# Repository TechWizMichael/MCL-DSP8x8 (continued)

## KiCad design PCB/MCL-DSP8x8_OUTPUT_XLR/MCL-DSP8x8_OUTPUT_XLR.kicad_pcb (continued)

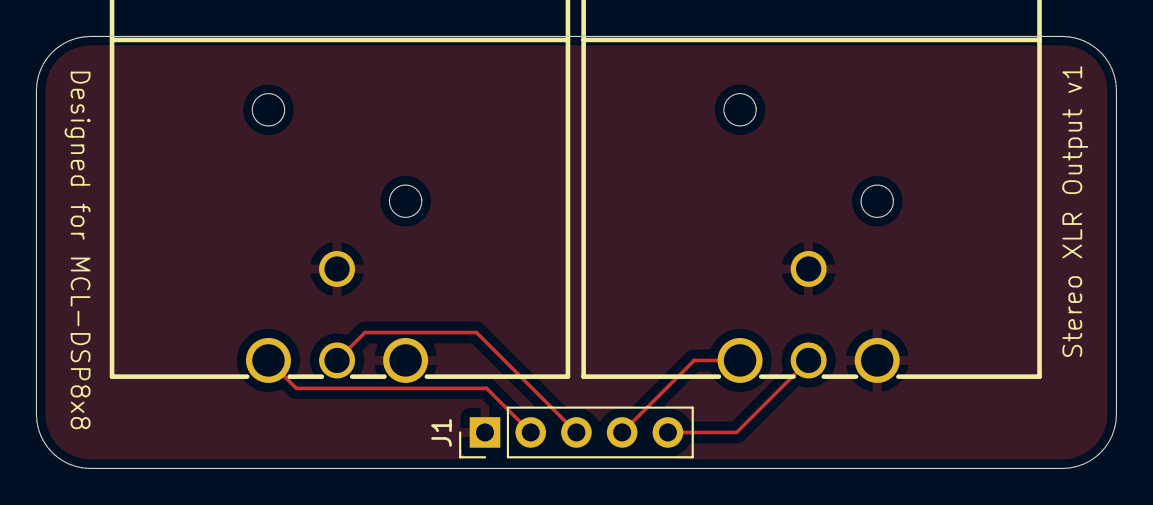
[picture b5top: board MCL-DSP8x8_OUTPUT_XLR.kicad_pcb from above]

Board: 2 copper layers, 60.0 x 24.0 mm, 3 parts (0 on the bottom side), 5 nets.

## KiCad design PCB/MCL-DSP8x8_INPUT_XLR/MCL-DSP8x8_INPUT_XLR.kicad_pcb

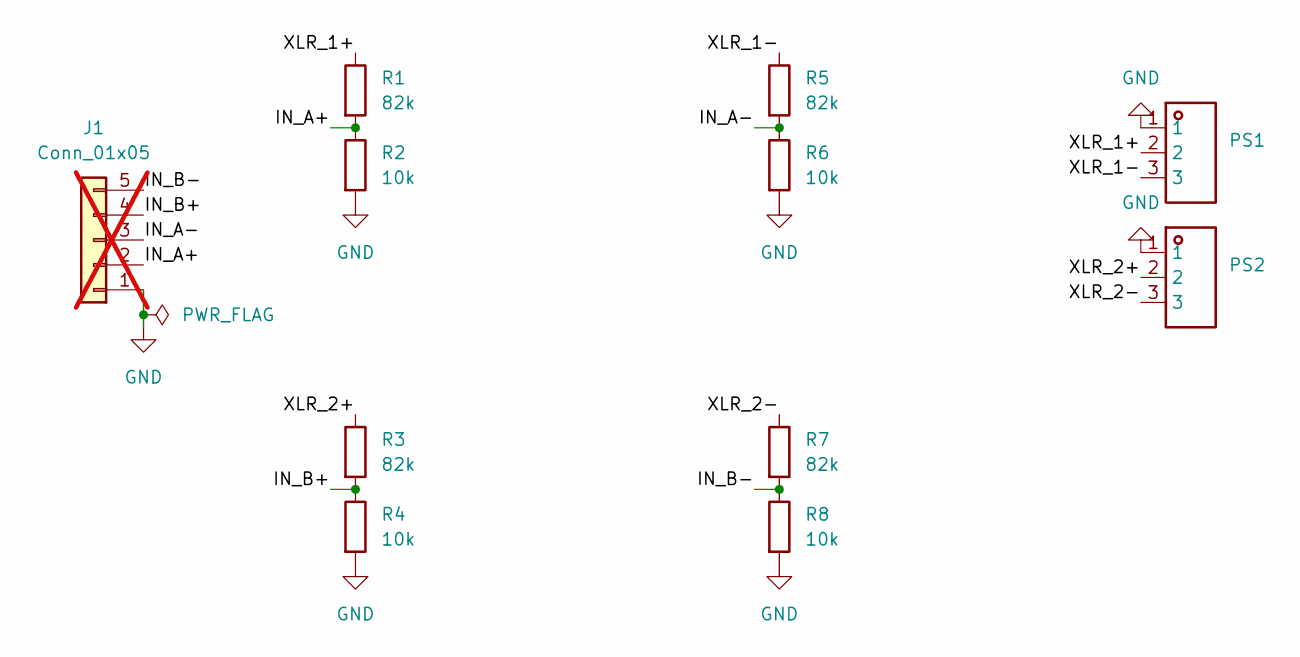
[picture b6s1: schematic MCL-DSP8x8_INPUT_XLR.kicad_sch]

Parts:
J1: Conn_01x05; PinHeader_1x05_P2.54mm_Vertical; not fitted
PS1, PS2: NC3FAAH1; Manufacturer Part NC3FAAH1; LCSC Part Name NC3FAAH1
R1, R3, R5, R7: 82k; R_0805_2012Metric_Pad1.20x1.40mm_HandSolder; LCSC Part # C22356755
R2, R4, R6, R8: 10k; R_0805_2012Metric_Pad1.20x1.40mm_HandSolder; LCSC Part # C3152175

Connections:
/IN_A+: J1.2, R1.2, R2.1
/IN_A-: J1.3, R5.2, R6.1
/IN_B+: J1.4, R3.2, R4.1
/IN_B-: J1.5, R7.2, R8.1
/XLR_1+: PS1.2, R1.1
/XLR_1-: PS1.3, R5.1
/XLR_2+: PS2.2, R3.1
/XLR_2-: PS2.3, R7.1
GND: J1.1, PS1.1, PS2.1, R2.2, R4.2, R6.2, R8.2

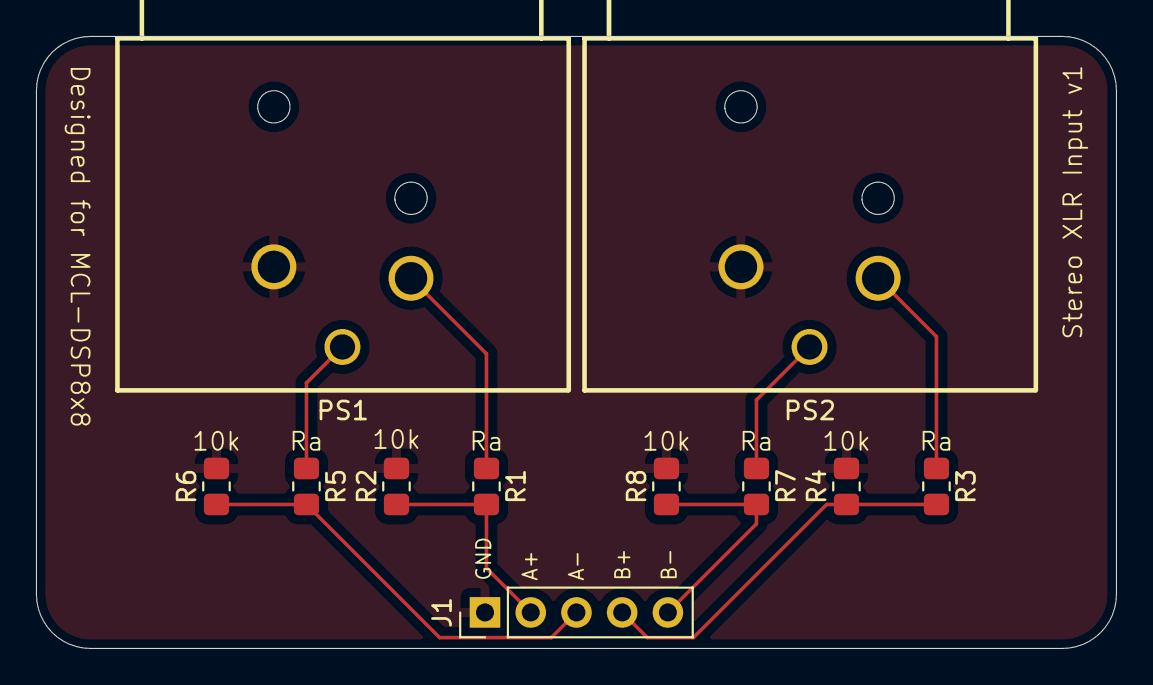
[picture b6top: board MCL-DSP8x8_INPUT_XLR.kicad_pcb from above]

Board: 2 copper layers, 60.0 x 34.0 mm, 11 parts (0 on the bottom side), 9 nets.

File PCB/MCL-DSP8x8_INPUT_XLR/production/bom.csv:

Designator,Footprint,Quantity,Value,LCSC Part #
J1,PinHeader_1x05_P2.54mm_Vertical,1,Conn_01x05,
"PS1, PS2",NC3FAAH1,2,~,
"R1, R3, R5, R7",R_Axial_DIN0207_L6.3mm_D2.5mm_P10.16mm_Horizontal,4,82k,
"R2, R4, R6, R8",R_Axial_DIN0207_L6.3mm_D2.5mm_P10.16mm_Horizontal,4,10k,

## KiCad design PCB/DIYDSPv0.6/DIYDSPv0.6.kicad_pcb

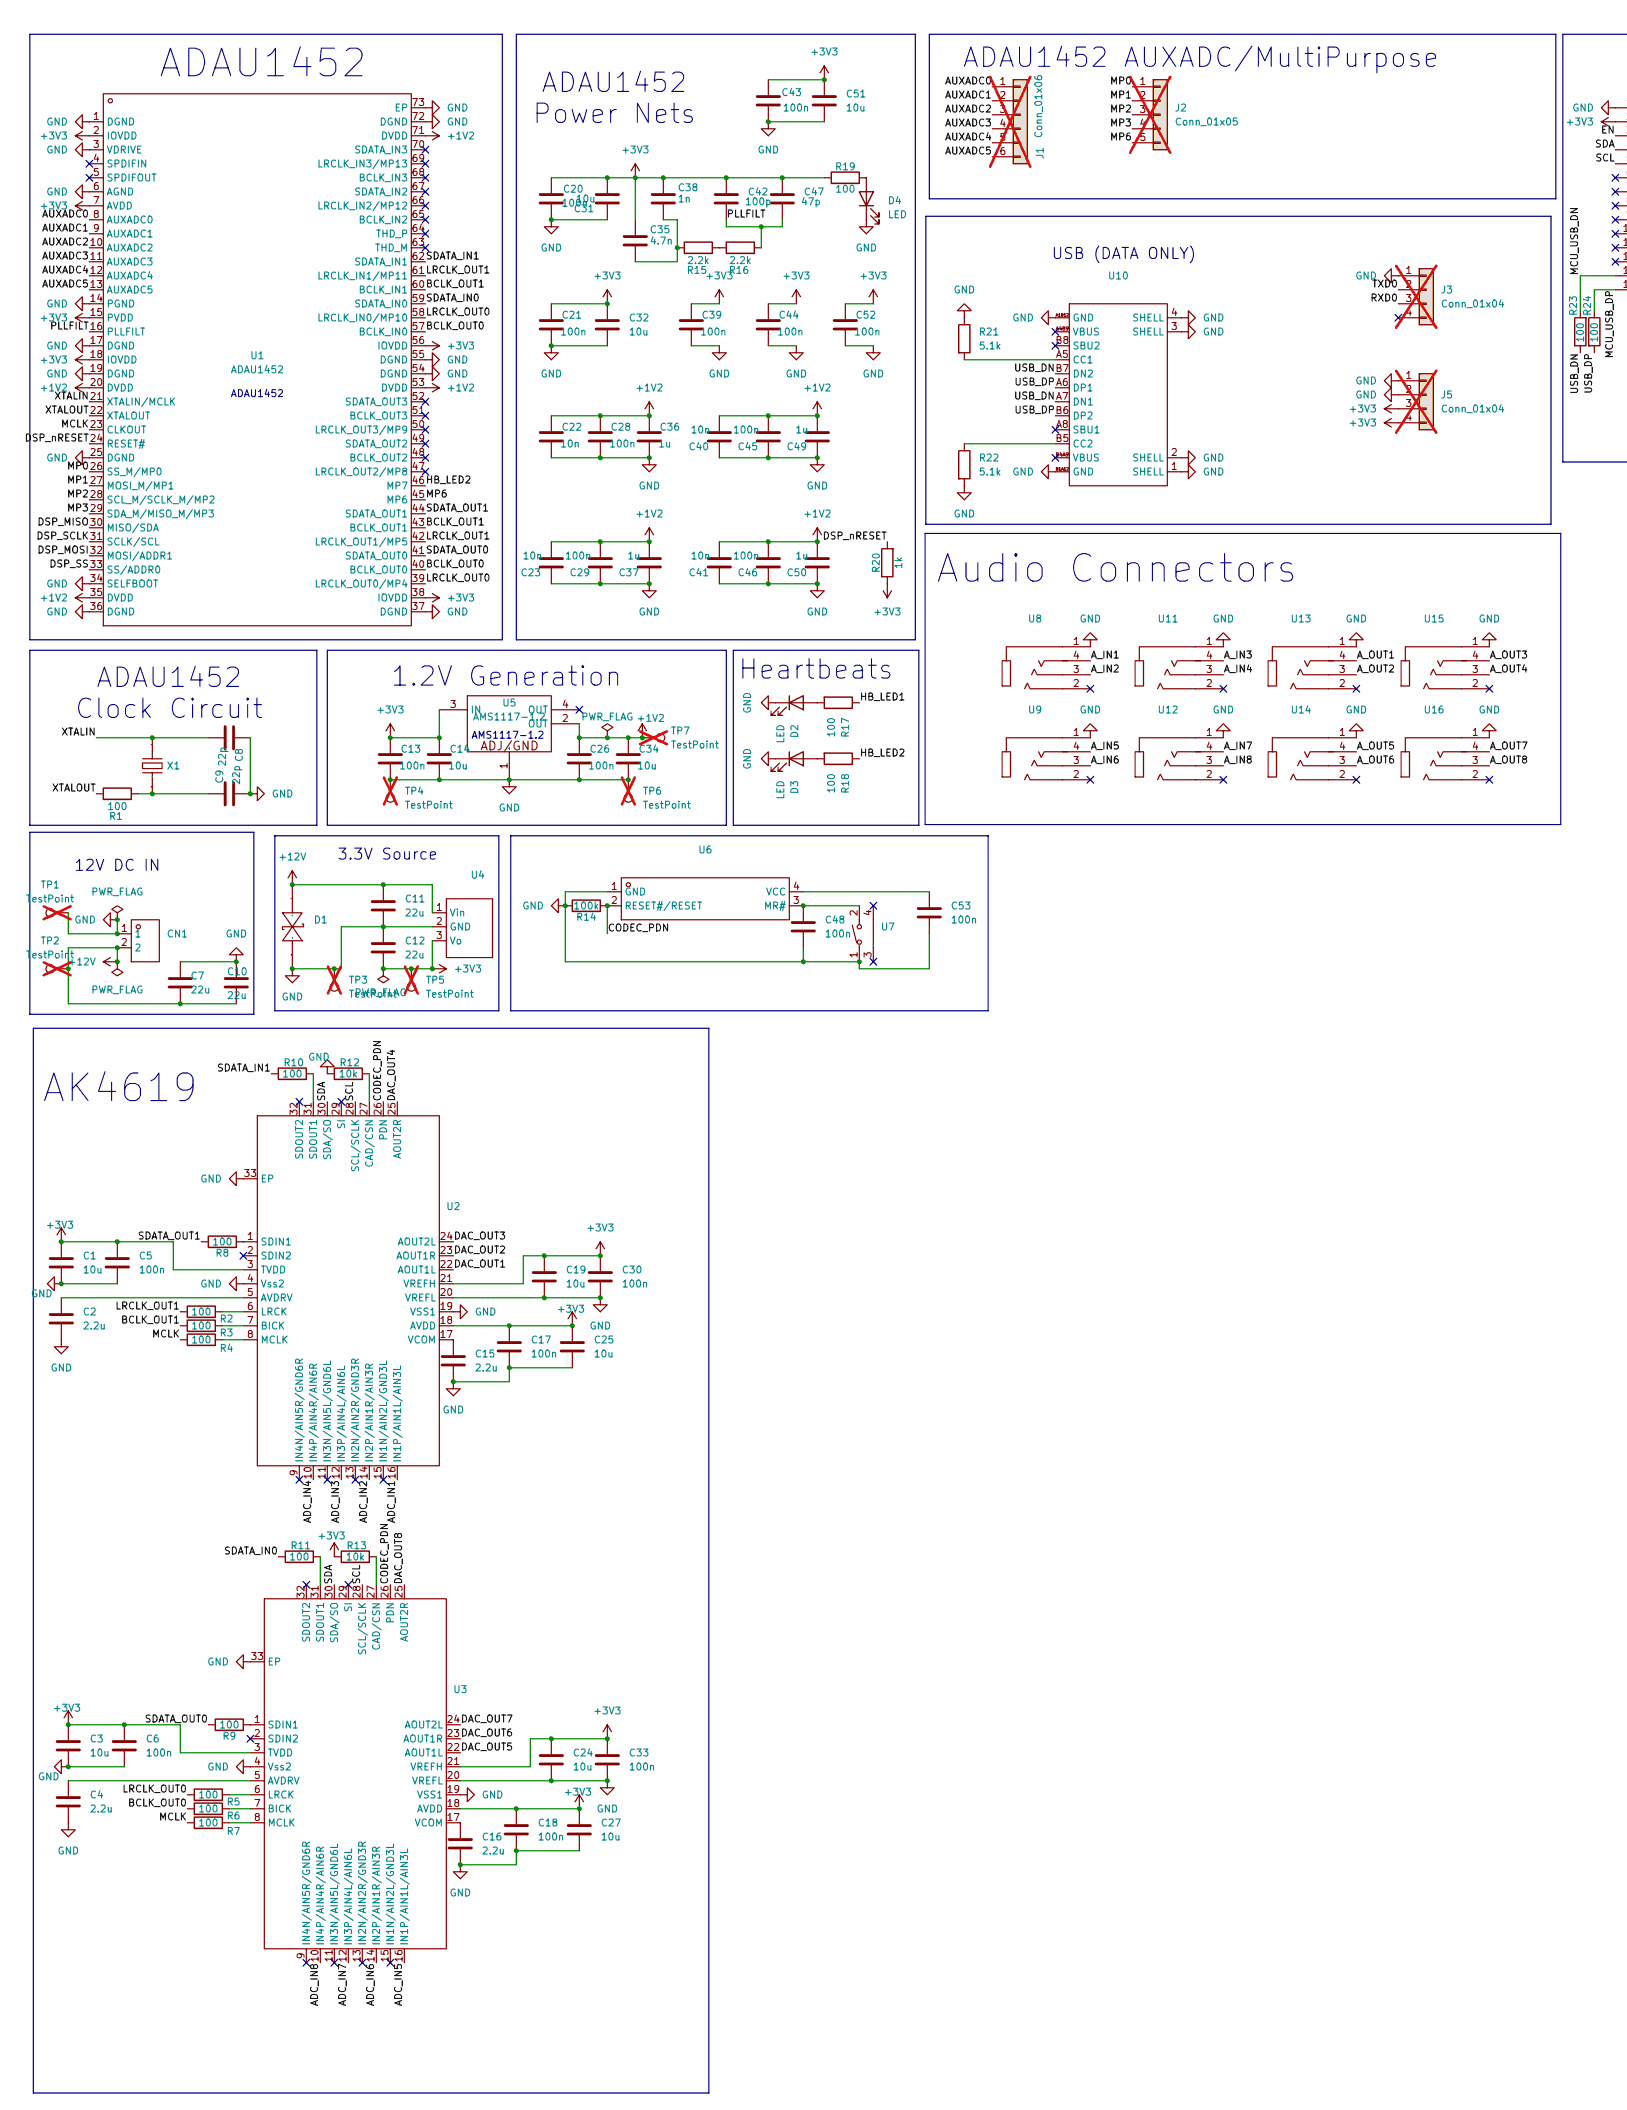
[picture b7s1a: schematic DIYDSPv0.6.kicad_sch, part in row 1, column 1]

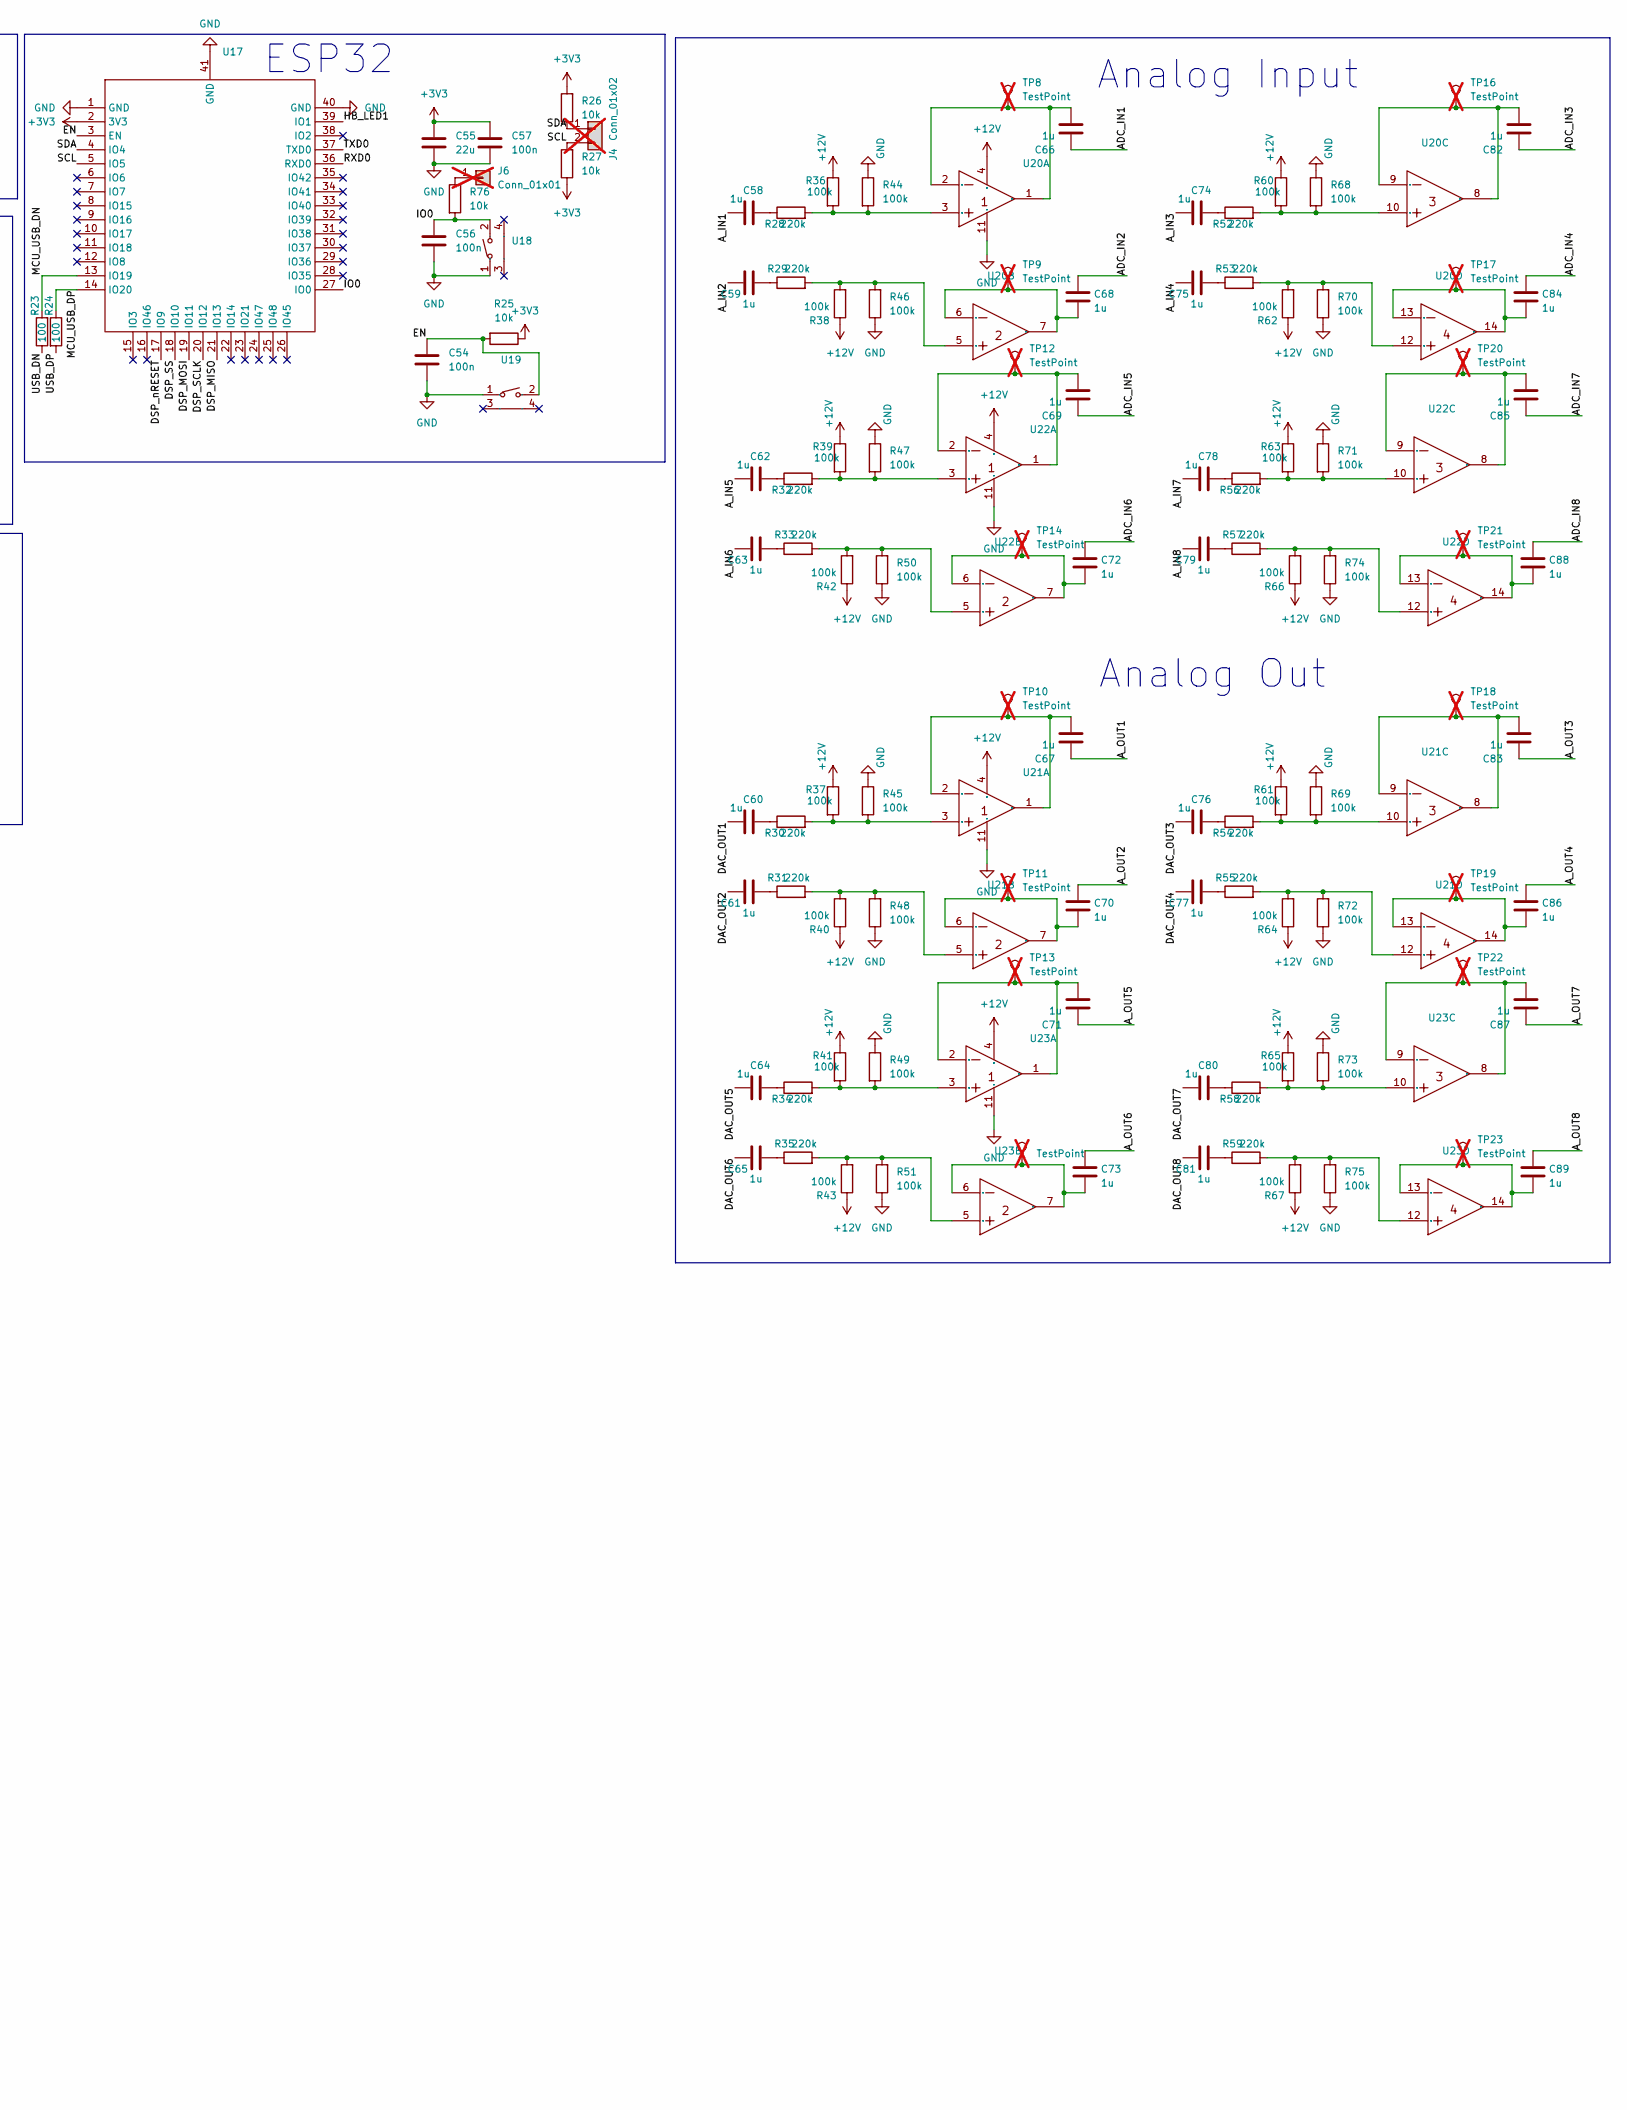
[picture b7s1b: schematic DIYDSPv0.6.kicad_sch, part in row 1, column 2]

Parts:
C1, C3, C14, C19, C24, C25, C27, C31, C32, C34, C51: 10u; C_0603_1608Metric; LCSC Part # C96446
C2, C4, C15, C16: 2.2u; C_0402_1005Metric; LCSC Part # C12530
C5, C6, C13, C17, C18, C20, C21, C26, C28, C29, C30, C33, C39, C43, C44, C45, C46, C48, C52, C53, C54, C56, C57: 100n; C_0402_1005Metric; LCSC Part # C307331
C7, C10, C11, C12, C55: 22u; C_0805_2012Metric; LCSC Part # C45783
C8, C9: 22p; C_0402_1005Metric; LCSC Part # C1555
C22, C23, C40, C41: 10n; C_0402_1005Metric; LCSC Part # C15195
C35: 4.7n; C_0402_1005Metric; LCSC Part # C1538
C36, C37, C49, C50, C58, C59, C60, C61, C62, C63, C64, C65, C66, C67, C68, C69, C70, C71, C72, C73, C74, C75, C76, C77, C78, C79, C80, C81, C82, C83, C84, C85, C86, C87, C88, C89: 1u; C_0402_1005Metric; LCSC Part # C52923
C38: 1n; C_0402_1005Metric; LCSC Part # C1523
C42: 100p; C_0402_1005Metric; LCSC Part # C1546
C47: 47p; C_0402_1005Metric; LCSC Part # C1567
CN1: MX126-5.0-02P-GN01-Cu-S-A; Manufacturer Part MX126-5.0-02P-GN01-Cu-S-A; LCSC Part Name 1x2P 5mm 直插 排数:1 每排P数:2
D1: SMF20CA; Manufacturer Part SMF20CA; LCSC Part Name 双向TVS 20V截止 峰值浪涌电流：6.2A
D2, D3, D4: LED; LED_0805_2012Metric; LCSC Part # C84256
J1: Conn_01x06; PinHeader_1x06_P2.54mm_Vertical; not fitted
J2: Conn_01x05; PinHeader_1x05_P2.54mm_Vertical; not fitted
J3, J5: Conn_01x04; PinHeader_1x04_P2.54mm_Vertical; not fitted
J4: Conn_01x02; PinHeader_1x02_P2.54mm_Vertical; not fitted
J6: Conn_01x01; PinHeader_1x01_P2.54mm_Vertical; not fitted
R1, R2, R3, R4, R5, R6, R7, R8, R9, R10, R11, R17, R18, R19, R23, R24: 100; R_0805_2012Metric; LCSC Part # C17408
R12, R13, R25, R26, R27, R76: 10k; R_0402_1005Metric; LCSC Part # C25744
R14, R36, R37, R38, R39, R40, R41, R42, R43, R44, R45, R46, R47, R48, R49, R50, R51, R60, R61, R62, R63, R64, R65, R66, R67, R68, R69, R70, R71, R72, R73, R74, R75: 100k; R_0402_1005Metric; LCSC Part # C25741
R15, R16: 2.2k; R_0402_1005Metric; LCSC Part # C25879
R20: 1k; R_0402_1005Metric; LCSC Part # C11702
R21, R22: 5.1k; R_0402_1005Metric; LCSC Part # C25905
R28, R29, R30, R31, R32, R33, R34, R35, R52, R53, R54, R55, R56, R57, R58, R59: 220k; R_0603_1608Metric; LCSC Part # C22961
TP1, TP3, TP4, TP6: TestPoint; TestPoint_THTPad_D4.0mm_Drill2.0mm; not fitted
TP2, TP5, TP7, TP8, TP9, TP10, TP11, TP12, TP13, TP14, TP15, TP16, TP17, TP18, TP19, TP20, TP21, TP22, TP23: TestPoint; TestPoint_THTPad_D2.0mm_Drill1.0mm; not fitted
U1: ADAU1452; ADAU1452WBCPZ-RL; Manufacturer Part ADAU1452WBCPZ-RL; LCSC Part Name SigmaDSP 数字音频处理器
U2, U3: AK4619VN; Manufacturer Part AK4619VN; LCSC Part Name AK4619VN
U4: K7803M-1000R3; Manufacturer Part K7803M-1000R3; LCSC Part Name DCDC电源模块
U5: AMS1117-1.2; Manufacturer Part AMS1117-1.2; LCSC Part Name 1.2V 1A 15V
U6: ADM811TARTZ-REEL7; Manufacturer Part ADM811TARTZ-REEL7; LCSC Part Name 4引脚SOT-143微处理器监控电路
U7, U18, U19: YTS1C0033BBG01; Manufacturer Part YTS1C0033BBG01; LCSC Part Name 侧按键3x6x3.8 黑钮贴片
U8, U9, U11, U12, U13, U14, U15, U16: PJ-320D; Manufacturer Part PJ-320D; LCSC Part Name 3.5mm耳机座
U10: GT-USB-7010ASV; Manufacturer Part GT-USB-7010ASV; LCSC Part Name Type-C 母 卧贴
U17: ESP32-S3-WROOM-1U-N8; Manufacturer Part ESP32-S3-WROOM-1U-N8; LCSC Part Name 通用型Wi-Fi+低功耗蓝牙MCU模组
U20, U21, U22, U23: LM324DT; Manufacturer Part LM324DT; LCSC Part Name 低功耗四路运算放大器
X1: 12.288MHz; S47SMD12.288M20PF20R30B3; Manufacturer Part S47SMD12.288M20PF20R30B3; LCSC Part Name 12.288MHz ±20ppm 20pF

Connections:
+1V2: C22.1, C23.2, C26.1, C28.1, C29.2, C34.1, C36.1, C37.2, C40.2, C41.2, C45.2, C46.2, C49.2, C50.2, TP7.1, U1.20 (DVDD), U1.35 (DVDD), U1.53 (DVDD), U1.71 (DVDD), U5.2 (OUT)
+3V3: C1.2, C3.2, C5.2, C6.2, C12.1, C13.1, C14.1, C17.2, C18.2, C19.2, C20.1, C21.1, C24.1, C25.1, C27.2, C30.2, C31.2, C32.1, C33.2, C35.1, C38.1, C39.1, C42.1, C43.1, C44.1, C47.1, C51.1, C52.1, C55.1, C57.1, J5.3, J5.4, R13.1, R19.1, R20.1, R25.1, R26.2, R27.1, TP5.1, U1.2 (IOVDD), U1.7 (AVDD), U1.15 (PVDD), U1.18 (IOVDD), U1.38 (IOVDD), U1.56 (IOVDD), U2.3 (TVDD), U2.18 (AVDD), U2.21 (VREFH), U3.3 (TVDD), U3.18 (AVDD), U3.21 (VREFH), U4.3 (Vo), U5.3 (IN), U17.2 (3V3)
+12V: C7.2, C10.2, C11.1, CN1.2, D1.2, R36.1, R37.1, R38.1, R39.1, R40.1, R41.1, R42.1, R43.1, R60.1, R61.1, R62.1, R63.1, R64.1, R65.1, R66.1, R67.1, TP2.1, U4.1 (Vin), U20.4 (VCC+), U21.4 (VCC+), U22.4 (VCC+), U23.4 (VCC+)
/ADC_IN1: C66.2, U2.16 (IN1P/AIN1L/AIN3L)
/ADC_IN2: C68.2, U2.14 (IN2P/AIN1R/AIN3R)
/ADC_IN3: C82.2, U2.12 (IN3P/AIN4L/AIN6L)
/ADC_IN4: C84.2, U2.10 (IN4P/AIN4R/AIN6R)
/ADC_IN5: C69.2, U3.16 (IN1P/AIN1L/AIN3L)
/ADC_IN6: C72.2, U3.14 (IN2P/AIN1R/AIN3R)
/ADC_IN7: C85.2, U3.12 (IN3P/AIN4L/AIN6L)
/ADC_IN8: C88.2, U3.10 (IN4P/AIN4R/AIN6R)
/AUXADC0: J1.1, U1.8 (AUXADC0)
/AUXADC1: J1.2, U1.9 (AUXADC1)
/AUXADC2: J1.3, U1.10 (AUXADC2)
/AUXADC3: J1.4, U1.11 (AUXADC3)
/AUXADC4: J1.5, U1.12 (AUXADC4)
/AUXADC5: J1.6, U1.13 (AUXADC5)
/A_IN1: C58.1, U8.4
/A_IN2: C59.1, U8.3
/A_IN3: C74.1, U11.4
/A_IN4: C75.1, U11.3
/A_IN5: C62.1, U9.4
/A_IN6: C63.1, U9.3
/A_IN7: C78.1, U12.4
/A_IN8: C79.1, U12.3
/A_OUT1: C67.2, U13.4
/A_OUT2: C70.2, U13.3
/A_OUT3: C83.2, U15.4
/A_OUT4: C86.2, U15.3
/A_OUT5: C71.2, U14.4
/A_OUT6: C73.2, U14.3
/A_OUT7: C87.2, U16.4
/A_OUT8: C89.2, U16.3
/BCLK_OUT0: R6.1, U1.40 (BCLK_OUT0), U1.57 (BCLK_IN0)
/BCLK_OUT1: R3.1, U1.43 (BCLK_OUT1), U1.60 (BCLK_IN1)
/CODEC_PDN: R14.2, U2.26 (PDN), U3.26 (PDN), U6.2 (RESET#/RESET)
/DAC_OUT1: C60.1, U2.22 (AOUT1L)
/DAC_OUT2: C61.1, U2.23 (AOUT1R)
/DAC_OUT3: C76.1, U2.24 (AOUT2L)
/DAC_OUT4: C77.1, U2.25 (AOUT2R)
/DAC_OUT5: C64.1, U3.22 (AOUT1L)
/DAC_OUT6: C65.1, U3.23 (AOUT1R)
/DAC_OUT7: C80.1, U3.24 (AOUT2L)
/DAC_OUT8: C81.1, U3.25 (AOUT2R)
/DSP_MISO: U1.30 (MISO/SDA), U17.21 (IO13)
/DSP_MOSI: U1.32 (MOSI/ADDR1), U17.19 (IO11)
/DSP_SCLK: U1.31 (SCLK/SCL), U17.20 (IO12)
/DSP_SS: U1.33 (SS/ADDR0), U17.18 (IO10)
/DSP_nRESET: R20.2, U1.24 (RESET#), U17.17 (IO9)
/EN: C54.1, R25.2, U17.3 (EN), U19.2
/HB_LED1: R17.1, U17.39 (IO1)
/HB_LED2: R18.1, U1.46 (MP7)
/IO0: C56.2, R76.2, U17.27 (IO0), U18.2
/LRCLK_OUT0: R5.1, U1.39 (LRCLK_OUT0/MP4), U1.58 (LRCLK_IN0/MP10)
/LRCLK_OUT1: R2.1, U1.42 (LRCLK_OUT1/MP5), U1.61 (LRCLK_IN1/MP11)
/MCLK: R4.1, R7.1, U1.23 (CLKOUT)
/MCU_USB_DN: R23.2, U17.13 (IO19)
/MCU_USB_DP: R24.1, U17.14 (IO20)
/MP0: J2.1, U1.26 (SS_M/MP0)
/MP1: J2.2, U1.27 (MOSI_M/MP1)
/MP2: J2.3, U1.28 (SCL_M/SCLK_M/MP2)
/MP3: J2.4, U1.29 (SDA_M/MISO_M/MP3)
/MP6: J2.5, U1.45 (MP6)
/PLLFILT: C42.2, C47.2, R16.2, U1.16 (PLLFILT)
/RXD0: J3.3, U17.36 (RXD0)
/SCL: J4.2, R27.2, U2.28 (SCL/SCLK), U3.28 (SCL/SCLK), U17.5 (IO5)
/SDA: J4.1, R26.1, U2.30 (SDA/SO), U3.30 (SDA/SO), U17.4 (IO4)
/SDATA_IN0: R11.1, U1.59 (SDATA_IN0)
/SDATA_IN1: R10.1, U1.62 (SDATA_IN1)
/SDATA_OUT0: R9.1, U1.41 (SDATA_OUT0)
/SDATA_OUT1: R8.1, U1.44 (SDATA_OUT1)
/TXD0: J3.2, U17.37 (TXD0)
/USB_DN: R23.1, U10.A7 (DN1), U10.B7 (DN2)
/USB_DP: R24.2, U10.A6 (DP1), U10.B6 (DP2)
/XTALIN: C8.2, U1.21 (XTALIN/MCLK), X1.2
/XTALOUT: R1.1, U1.22 (XTALOUT)
GND: C1.1, C2.1, C3.1, C4.1, C5.1, C6.1, C7.1, C8.1, C9.2, C10.1, C11.2, C12.2, C13.2, C14.2, C15.1, C16.1, C17.1, C18.1, C19.1, C20.2, C21.2, C22.2, C23.1, C24.2, C25.2, C26.2, C27.1, C28.2, C29.1, C30.1, C31.1, C32.2, C33.1, C34.2, C36.2, C37.1, C39.2, C40.1, C41.1, C43.2, C44.2, C45.1, C46.1, C48.1, C49.1, C50.1, C51.2, C52.2, C53.1, C54.2, C55.2, C56.1, C57.2, CN1.1, D1.1, D2.1 (K), D3.1 (K), D4.1 (K), J3.1, J5.1, J5.2, R12.1, R14.1, R21.1, R22.2, R44.1, R45.1, R46.1, R47.1, R48.1, R49.1, R50.1, R51.1, R68.1, R69.1, R70.1, R71.1, R72.1, R73.1, R74.1, R75.1, TP1.1, TP3.1, TP4.1, TP6.1, U1.1 (DGND), U1.3 (VDRIVE), U1.6 (AGND), U1.14 (PGND), U1.17 (DGND), U1.19 (DGND), U1.25 (DGND), U1.34 (SELFBOOT), U1.36 (DGND), U1.37 (DGND), U1.54 (DGND), U1.55 (DGND), U1.72 (DGND), U1.73 (EP), U2.4 (Vss2), U2.19 (VSS1), U2.20 (VREFL), U2.33 (EP), U3.4 (Vss2), U3.19 (VSS1), U3.20 (VREFL), U3.33 (EP), U4.2 (GND), U5.1 (ADJ/GND), U6.1 (GND), U7.1, U8.1, U9.1, U10.1 (SHELL), U10.2 (SHELL), U10.3 (SHELL), U10.4 (SHELL), U10.A1B12 (GND), U10.B1A12 (GND), U11.1, U12.1, U13.1, U14.1, U15.1, U16.1, U17.1 (GND), U17.40 (GND), U17.41 (GND), U18.1, U19.1, U20.11 (VCC-), U21.11 (VCC-), U22.11 (VCC-), U23.11 (VCC-)
unnamed: C9.1, R1.2, X1.1
unnamed: C35.2, C38.2, R15.1
unnamed: C58.2, R28.1
unnamed: C59.2, R29.1
unnamed: C60.2, R30.1
unnamed: C61.2, R31.1
unnamed: C62.2, R32.1
unnamed: C63.2, R33.1
unnamed: C64.2, R34.1
unnamed: C65.2, R35.1
unnamed: C74.2, R52.1
unnamed: C75.2, R53.1
unnamed: C76.2, R54.1
unnamed: C77.2, R55.1
unnamed: C78.2, R56.1
unnamed: C79.2, R57.1
unnamed: C80.2, R58.1
unnamed: C81.2, R59.1
unnamed: D2.2 (A), R17.2
unnamed: D3.2 (A), R18.2
unnamed: D4.2 (A), R19.2
unnamed: J6.1, R76.1
unnamed: R15.2, R16.1
unnamed: C2.2, U2.5 (AVDRV)
unnamed: R3.2, U2.7 (BICK)
unnamed: R12.2, U2.27 (CAD/CSN)
unnamed: R2.2, U2.6 (LRCK)
unnamed: R4.2, U2.8 (MCLK)
unnamed: R8.2, U2.1 (SDIN1)
unnamed: R10.2, U2.31 (SDOUT1)
unnamed: C15.2, U2.17 (VCOM)
unnamed: C4.2, U3.5 (AVDRV)
unnamed: R6.2, U3.7 (BICK)
unnamed: R13.2, U3.27 (CAD/CSN)
unnamed: R5.2, U3.6 (LRCK)
unnamed: R7.2, U3.8 (MCLK)
unnamed: R9.2, U3.1 (SDIN1)
unnamed: R11.2, U3.31 (SDOUT1)
unnamed: C16.2, U3.17 (VCOM)
unnamed: C48.2, U6.3 (MR#), U7.2
unnamed: C53.2, U6.4 (VCC)
unnamed: R21.2, U10.A5 (CC1)
unnamed: R22.1, U10.B5 (CC2)
unnamed: R28.2, R36.2, R44.2, U20.3 (IN1+)
unnamed: C66.1, TP8.1, U20.1 (OUT1), U20.2 (IN1-)
unnamed: R29.2, R38.2, R46.2, U20.5 (IN2+)
unnamed: C68.1, TP9.1, U20.6 (IN2-), U20.7 (OUT2)
unnamed: R52.2, R60.2, R68.2, U20.10 (IN3+)
unnamed: C82.1, TP16.1, U20.8 (OUT3), U20.9 (IN3-)
unnamed: R53.2, R62.2, R70.2, U20.12 (IN4+)
unnamed: C84.1, TP17.1, U20.13 (IN4-), U20.14 (OUT4)
unnamed: R30.2, R37.2, R45.2, U21.3 (IN1+)
unnamed: C67.1, TP10.1, U21.1 (OUT1), U21.2 (IN1-)
unnamed: R31.2, R40.2, R48.2, U21.5 (IN2+)
unnamed: C70.1, TP11.1, U21.6 (IN2-), U21.7 (OUT2)
unnamed: R54.2, R61.2, R69.2, U21.10 (IN3+)
unnamed: C83.1, TP18.1, U21.8 (OUT3), U21.9 (IN3-)
unnamed: R55.2, R64.2, R72.2, U21.12 (IN4+)
unnamed: C86.1, TP19.1, U21.13 (IN4-), U21.14 (OUT4)
unnamed: R32.2, R39.2, R47.2, U22.3 (IN1+)
unnamed: C69.1, TP12.1, U22.1 (OUT1), U22.2 (IN1-)
unnamed: R33.2, R42.2, R50.2, U22.5 (IN2+)
unnamed: C72.1, TP14.1, U22.6 (IN2-), U22.7 (OUT2)
unnamed: R56.2, R63.2, R71.2, U22.10 (IN3+)
unnamed: C85.1, TP20.1, U22.8 (OUT3), U22.9 (IN3-)
unnamed: R57.2, R66.2, R74.2, U22.12 (IN4+)
unnamed: C88.1, TP21.1, U22.13 (IN4-), U22.14 (OUT4)
unnamed: R34.2, R41.2, R49.2, U23.3 (IN1+)
unnamed: C71.1, TP13.1, U23.1 (OUT1), U23.2 (IN1-)
unnamed: R35.2, R43.2, R51.2, U23.5 (IN2+)
unnamed: C73.1, TP15.1, U23.6 (IN2-), U23.7 (OUT2)
unnamed: R58.2, R65.2, R73.2, U23.10 (IN3+)
unnamed: C87.1, TP22.1, U23.8 (OUT3), U23.9 (IN3-)
unnamed: R59.2, R67.2, R75.2, U23.12 (IN4+)
unnamed: C89.1, TP23.1, U23.13 (IN4-), U23.14 (OUT4)

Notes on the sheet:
ESP32
ADAU1452
ADAU1452 Power Nets
Analog Out
1.2V Generation
Audio Connectors
AMS1117-1.2
Heartbeats
USB (DATA ONLY)
AK4619
3.3V Source
ADAU1452 AUXADC/MultiPurpose
ADAU1452 Clock Circuit
12V DC IN
Analog Input

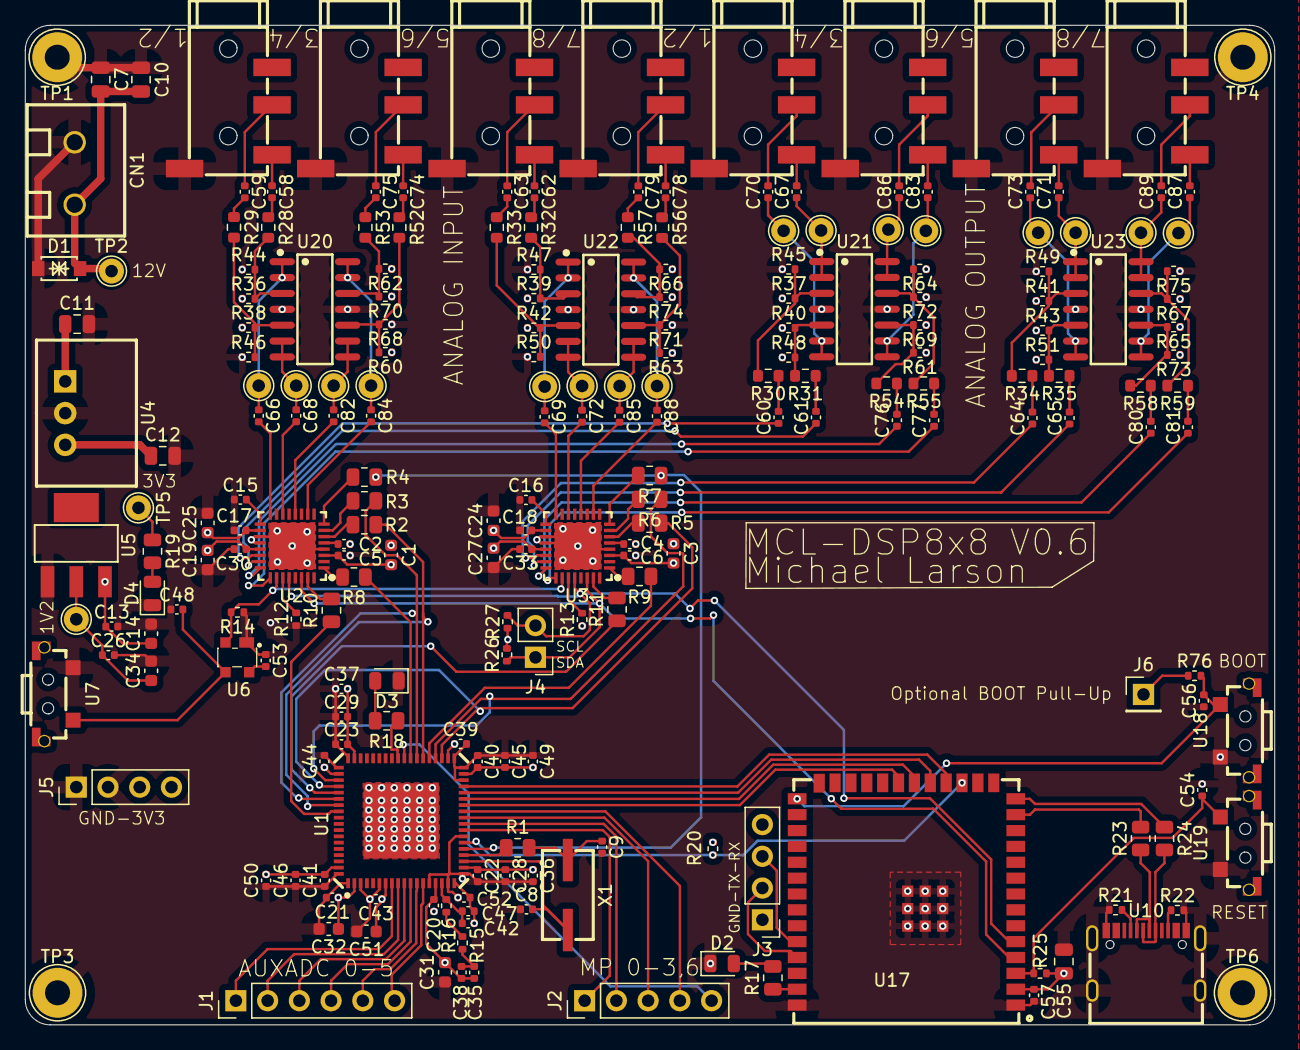
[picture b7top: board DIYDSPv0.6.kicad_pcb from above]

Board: 4 copper layers, 100.0 x 80.0 mm, 223 parts (0 on the bottom side), 152 nets.

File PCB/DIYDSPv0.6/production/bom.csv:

Designator,Footprint,Quantity,Value,LCSC Part #
"C1, C14, C19, C24, C25, C27, C3, C31, C32, C34, C51",0603,11,10u,C96446
"C10, C11, C12, C55, C7",0805,5,22u,C45783
"C13, C17, C18, C20, C21, C26, C28, C29, C30, C33, C39, C43, C44, C45, C46, C48, C5, C52, C53, C54, C56, C57, C6",0402,23,100n,C307331
"C15, C16, C2, C4",0402,4,2.2u,C12530
"C22, C23, C40, C41",0402,4,10n,C15195
C35,0402,1,4.7n,C1538
"C36, C37, C49, C50, C58, C59, C60, C61, C62, C63, C64, C65, C66, C67, C68, C69, C70, C71, C72, C73, C74, C75, C76, C77, C78, C79, C80, C81, C82, C83, C84, C85, C86, C87, C88, C89",0402,36,1u,C52923
C38,0402,1,1n,C1523
C42,0402,1,100p,C1546
C47,0402,1,47p,C1567
"C8, C9",0402,2,22p,C1555
CN1,MX126-5.0-02P-GN01-Cu-S-A,1,~,C5188434
D1,SMF20CA,1,~,C42371747
"D2, D3, D4",0805,3,LED,C84256
"R1, R10, R11, R17, R18, R19, R2, R23, R24, R3, R4, R5, R6, R7, R8, R9",0805,16,100, C17408
"R12, R13, R25, R26, R27, R76",0402,6,10k,C25744
"R14, R36, R37, R38, R39, R40, R41, R42, R43, R44, R45, R46, R47, R48, R49, R50, R51, R60, R61, R62, R63, R64, R65, R66, R67, R68, R69, R70, R71, R72, R73, R74, R75",0402,33,100k,C25741
"R15, R16",0402,2,2.2k, C25879
R20,0402,1,1k,C11702
"R21, R22",0402,2,5.1k, C25905
"R28, R29, R30, R31, R32, R33, R34, R35, R52, R53, R54, R55, R56, R57, R58, R59",0603,16,220k, C22961
U1,ADAU1452WBCPZ-RL,1,ADAU1452,C462188
U10,GT-USB-7010ASV,1,~,C2988369
"U11, U12, U13, U14, U15, U16, U8, U9",PJ-320D,8,~,C22459515
U17,ESP32-S3-WROOM-1U-N8,1,~,C3013946
"U18, U19, U7",YTS1C0033BBG01,3,~,C5188566
"U2, U3",AK4619VN,2,~,C3034747
"U20, U21, U22, U23",LM324DT,4,~,C71035
U4,K7803M-1000R3,1,~,C22749779
U5,AMS1117-1.2,1,AMS1117-1.2,C2992568
U6,ADM811TARTZ-REEL7,1,~,C462205
X1,S47SMD12.288M20PF20R30B3,1,12.288MHz,C5346044
